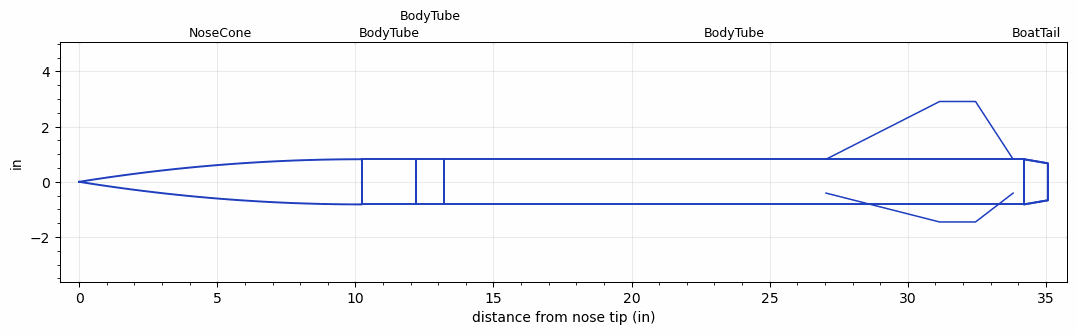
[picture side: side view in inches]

<RASAeroDocument>
 <FileVersion>2</FileVersion>
 <RocketDesign>
  <NoseCone>
   <Length>10.2362</Length>
   <Diameter>1.635</Diameter>
   <Shape>Tangent Ogive</Shape>
   <Location>0</Location>
  </NoseCone>
  <BodyTube>
   <Length>1.9685</Length>
   <Diameter>1.635</Diameter>
   <Location>10.2362</Location>
  </BodyTube>
  <BodyTube>
   <Length>1</Length>
   <Diameter>1.635</Diameter>
   <Location>12.2047</Location>
  </BodyTube>
  <BodyTube>
   <Length>21</Length>
   <Diameter>1.635</Diameter>
   <RailGuideDiameter>0.3819</RailGuideDiameter>
   <RailGuideHeight>0.3819</RailGuideHeight>
   <Location>13.2047</Location>
   <BoattailLength>0.8661</BoattailLength>
   <BoattailRearDiameter>1.3386</BoattailRearDiameter>
   <Fin>
    <Count>3</Count>
    <Chord>6.7716</Chord>
    <Span>2.09</Span>
    <SweepDistance>4.112</SweepDistance>
    <TipChord>1.299</TipChord>
    <Thickness>0.1181</Thickness>
    <Location>7.1653</Location>
    <AirfoilSection>Subsonic NACA</AirfoilSection>
   </Fin>
  </BodyTube>
  <BoatTail>
   <Length>0.8661</Length>
   <Diameter>1.635</Diameter>
   <RearDiameter>1.3386</RearDiameter>
   <Location>34.2047</Location>
  </BoatTail>
  <Surface>Camouflage Paint</Surface>
  <ModifiedBarrowman>False</ModifiedBarrowman>
  <Turbulence>True</Turbulence>
  <UseBooster1>False</UseBooster1>
  <UseBooster2>False</UseBooster2>
 </RocketDesign>
 <LaunchSite>
  <Altitude>0</Altitude>
  <Pressure>29.92</Pressure>
  <RodAngle>0</RodAngle>
  <RodLength>10</RodLength>
  <Temperature>91.4</Temperature>
  <WindSpeed>6.93</WindSpeed>
 </LaunchSite>
 <Recovery>
  <Altitude1>656.168</Altitude1>
  <Altitude2>300</Altitude2>
  <DeviceType1>Parachute</DeviceType1>
  <DeviceType2>Parachute</DeviceType2>
  <Event1>True</Event1>
  <Event2>True</Event2>
  <Size1>9</Size1>
  <Size2>30</Size2>
  <EventType1>Apogee</EventType1>
  <EventType2>Altitude</EventType2>
  <CD1>0.75</CD1>
  <CD2>0.75</CD2>
 </Recovery>
 <SimulationList>
  <Simulation>
   <SustainerEngine>I205  (AT)</SustainerEngine>
   <SustainerLaunchWt>1.68</SustainerLaunchWt>
   <SustainerCG>21.54</SustainerCG>
   <SustainerIgnitionDelay>0</SustainerIgnitionDelay>
   <Booster1SeparationDelay>0</Booster1SeparationDelay>
   <Booster1IgnitionDelay>0</Booster1IgnitionDelay>
   <IncludeBooster1>False</IncludeBooster1>
   <Booster2Delay>0</Booster2Delay>
   <IncludeBooster2>False</IncludeBooster2>
   <TimetoApogee>13.87022</TimetoApogee>
   <MaxAltitude>4964.422</MaxAltitude>
   <MaxVelocity>1186.509</MaxVelocity>
   <OptimumWt>2.184</OptimumWt>
   <OptimumMaxAlt>2.184</OptimumMaxAlt>
  </Simulation>
  <Simulation>
   <SustainerLaunchWt>1.6751</SustainerLaunchWt>
   <SustainerCG>21.5413</SustainerCG>
   <SustainerIgnitionDelay>0</SustainerIgnitionDelay>
   <Booster1SeparationDelay>0</Booster1SeparationDelay>
   <Booster1IgnitionDelay>0</Booster1IgnitionDelay>
   <IncludeBooster1>False</IncludeBooster1>
   <Booster2Delay>0</Booster2Delay>
   <IncludeBooster2>False</IncludeBooster2>
  </Simulation>
  <Simulation>
   <SustainerLaunchWt>1.6751</SustainerLaunchWt>
   <SustainerCG>21.5413</SustainerCG>
   <SustainerIgnitionDelay>0</SustainerIgnitionDelay>
   <Booster1SeparationDelay>0</Booster1SeparationDelay>
   <Booster1IgnitionDelay>0</Booster1IgnitionDelay>
   <IncludeBooster1>False</IncludeBooster1>
   <Booster2Delay>0</Booster2Delay>
   <IncludeBooster2>False</IncludeBooster2>
  </Simulation>
  <Simulation>
   <SustainerLaunchWt>1.6751</SustainerLaunchWt>
   <SustainerCG>21.5413</SustainerCG>
   <SustainerIgnitionDelay>0</SustainerIgnitionDelay>
   <Booster1SeparationDelay>0</Booster1SeparationDelay>
   <Booster1IgnitionDelay>0</Booster1IgnitionDelay>
   <IncludeBooster1>False</IncludeBooster1>
   <Booster2Delay>0</Booster2Delay>
   <IncludeBooster2>False</IncludeBooster2>
  </Simulation>
  <Simulation>
   <SustainerLaunchWt>1.6751</SustainerLaunchWt>
   <SustainerCG>21.5413</SustainerCG>
   <SustainerIgnitionDelay>0</SustainerIgnitionDelay>
   <Booster1SeparationDelay>0</Booster1SeparationDelay>
   <Booster1IgnitionDelay>0</Booster1IgnitionDelay>
   <IncludeBooster1>False</IncludeBooster1>
   <Booster2Delay>0</Booster2Delay>
   <IncludeBooster2>False</IncludeBooster2>
  </Simulation>
  <Simulation>
   <SustainerLaunchWt>1.6751</SustainerLaunchWt>
   <SustainerCG>21.5413</SustainerCG>
   <SustainerIgnitionDelay>0</SustainerIgnitionDelay>
   <Booster1SeparationDelay>0</Booster1SeparationDelay>
   <Booster1IgnitionDelay>0</Booster1IgnitionDelay>
   <IncludeBooster1>False</IncludeBooster1>
   <Booster2Delay>0</Booster2Delay>
   <IncludeBooster2>False</IncludeBooster2>
  </Simulation>
 </SimulationList>
</RASAeroDocument>
